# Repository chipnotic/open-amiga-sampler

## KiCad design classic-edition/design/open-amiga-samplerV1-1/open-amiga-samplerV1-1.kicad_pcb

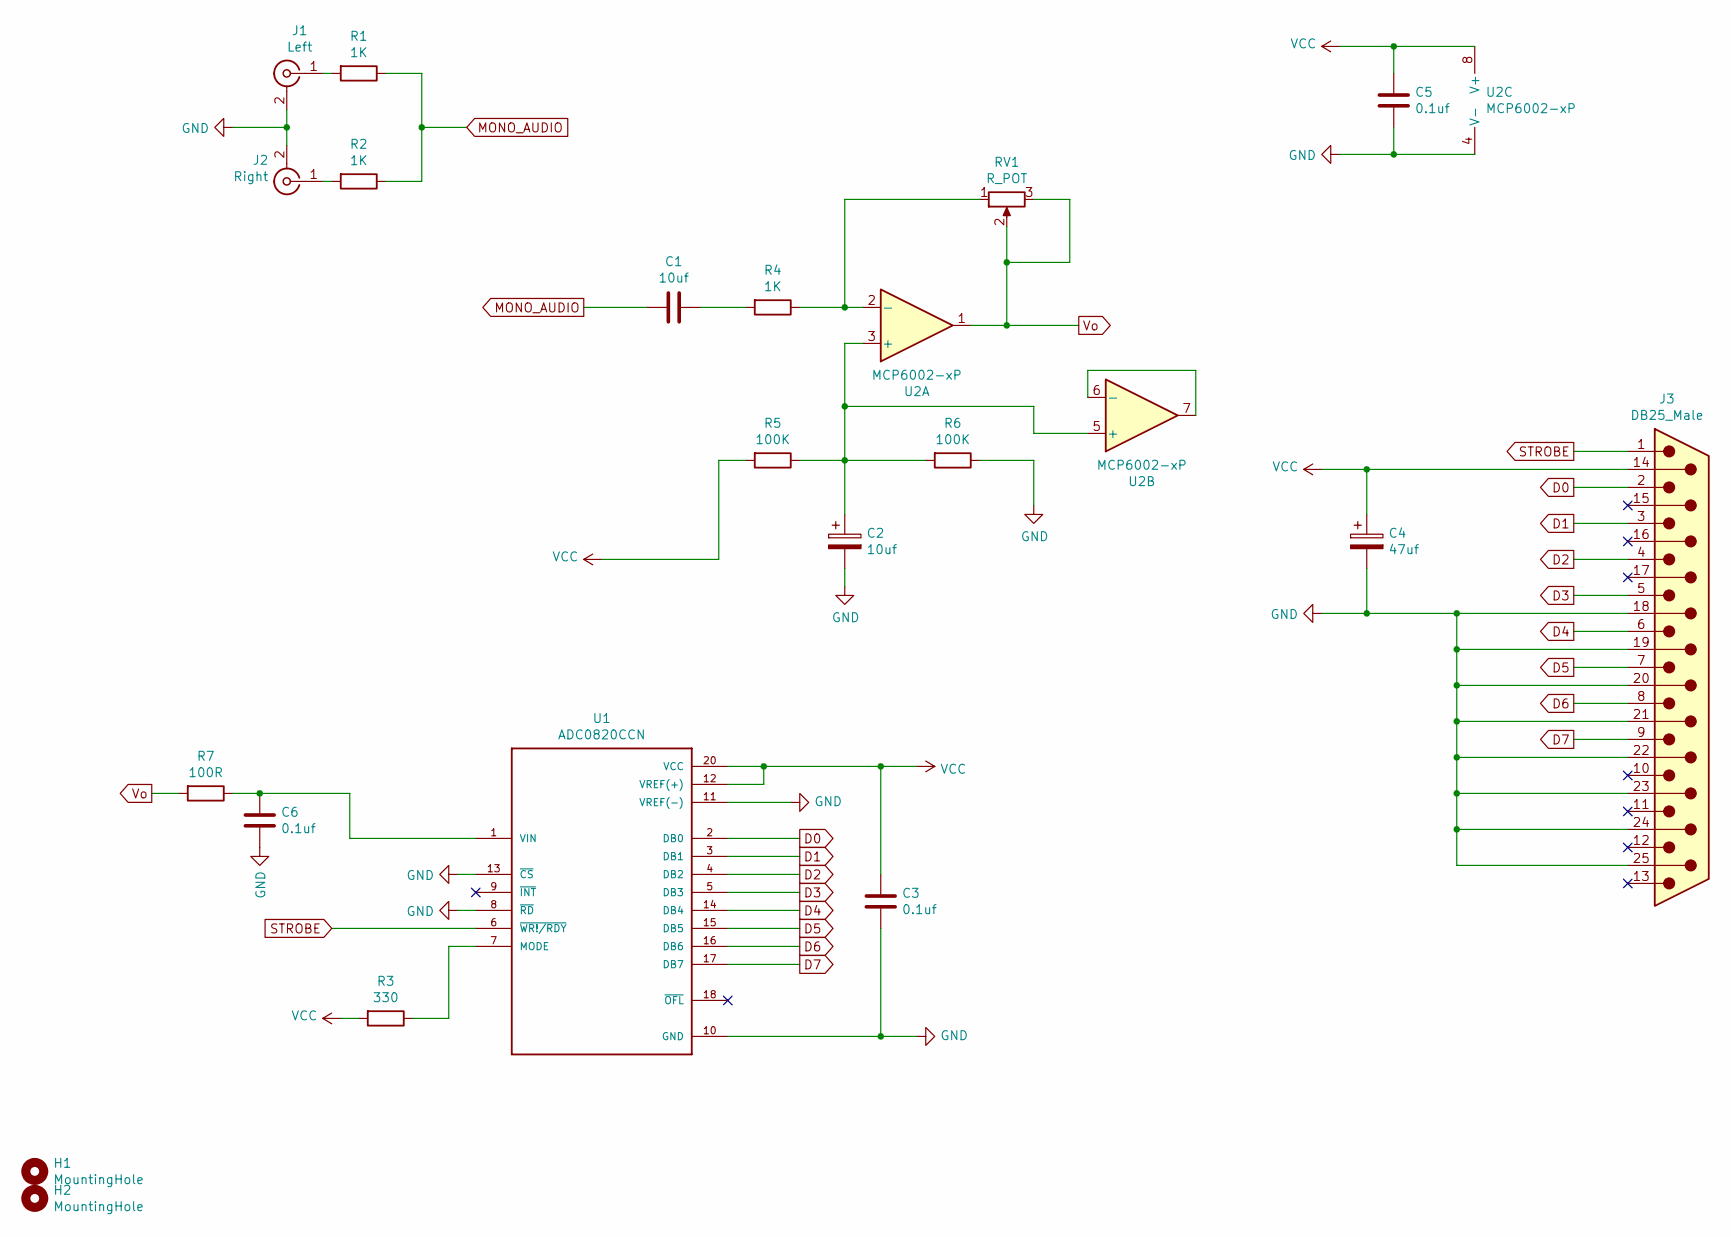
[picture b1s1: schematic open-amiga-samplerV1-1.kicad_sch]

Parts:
C1: 10uf; CP_Radial_Tantal_D5.5mm_P2.50mm; Mouser 581-TAP106K010DTW
C2: 10uf; CP_Radial_D4.0mm_P1.50mm; Mouser 647-UMP1A100MDD1TP
C3, C5, C6: 0.1uf; C_Disc_D3.4mm_W2.1mm_P2.50mm
C4: 47uf; CP_Radial_D5.0mm_P2.00mm; Mouser 647-URS1A470MDD1TA
H1, H2: MountingHole; MountingHole_2.2mm_M2
J1: Left; Audio pads; Mouser 490-RCJ-032
J2: Right; Audio pads; Mouser 490-RCJ-031
J3: DB25_Male; DSUB-25_Male_EdgeMount_P2.77mm; Mouser 601-40-9725M
R1, R2, R4: 1K; R_Axial_DIN0207_L6.3mm_D2.5mm_P10.16mm_Horizontal
R3: 330; R_Axial_DIN0207_L6.3mm_D2.5mm_P10.16mm_Horizontal
R5, R6: 100K; R_Axial_DIN0207_L6.3mm_D2.5mm_P10.16mm_Horizontal
R7: 100R; R_Axial_DIN0207_L6.3mm_D2.5mm_P10.16mm_Horizontal
RV1: R_POT; Pot pads; Mouser 858-P160KN-0QC20A10K
U1: ADC0820CCN; DIP-20_W7.62mm_Socket; Mouser 700-ADC0820CCN
U2: MCP6002-xP; DIP-8_W7.62mm_Socket; Mouser 579-MCP6002-I/P

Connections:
D0: J3.2, U1.2 (DB0)
D1: J3.3, U1.3 (DB1)
D2: J3.4, U1.4 (DB2)
D3: J3.5, U1.5 (DB3)
D4: J3.6, U1.14 (DB4)
D5: J3.7, U1.15 (DB5)
D6: J3.8, U1.16 (DB6)
D7: J3.9, U1.17 (DB7)
GND: C2.2, C3.2, C4.2, C5.2, C6.2, J1.2 (Ext), J2.2 (Ext), J3.18, J3.19, J3.20, J3.21, J3.22, J3.23, J3.24, J3.25, R6.1, U1.8 (~RD), U1.10 (GND), U1.11 (VREF(-)), U1.13 (~CS), U2.4 (V-)
MONO_AUDIO: C1.1, R1.1, R2.1
unnamed: C1.2, R4.2
unnamed: J1.1 (In), R1.2
unnamed: J2.1 (In), R2.2
unnamed: R3.1, U1.7 (MODE)
unnamed: R4.1, RV1.1, U2.2 (-)
unnamed: C6.1, R7.1, U1.1 (VIN)
unnamed: C2.1, R5.1, R6.2, U2.3 (+), U2.5 (+)
unnamed: U2.6 (-), U2.7
STROBE: J3.1, U1.6 (~WR!/RDY)
VCC: C3.1, C4.1, C5.1, J3.14, R3.2, R5.2, U1.12 (VREF(+)), U1.20 (VCC), U2.8 (V+)
Vo: R7.2, RV1.2, RV1.3, U2.1

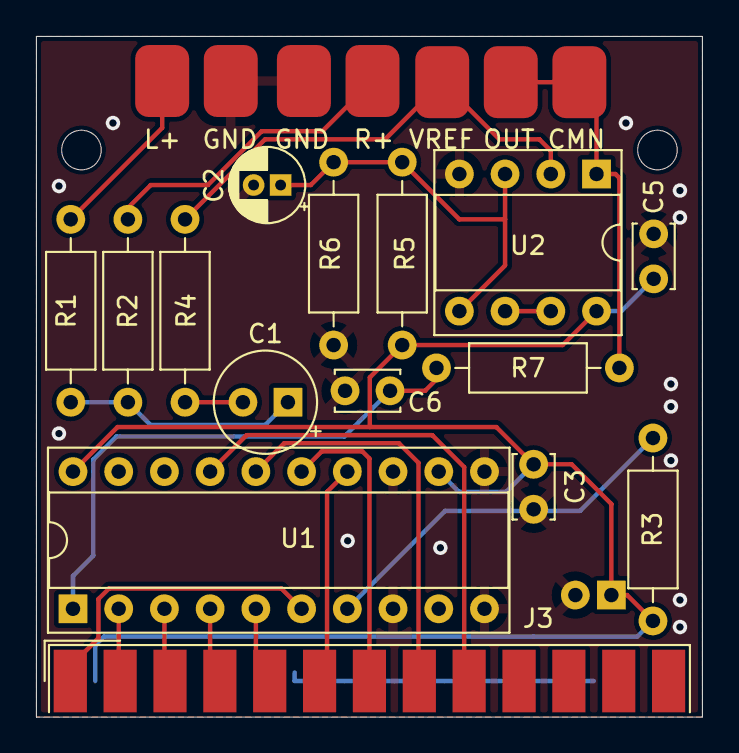
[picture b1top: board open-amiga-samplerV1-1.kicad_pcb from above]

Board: 2 copper layers, 37.0 x 37.8 mm, 21 parts (1 on the bottom side), 21 nets.

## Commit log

2022-03-19 Changes for V1.1
    Added changes to sampler as per gwEm303's V1.1 suggestions:
    DC Offset Fix - R5/R6 changed to 100k.
    C1 changed to tantalum.
    Connected unused op-amp.
    Added R7/C6 as "simple anti-aliasing filter (1st order)".
    PCB enlarged slightly to accommodate the new components, mounting holes not changed PCB just extended behind making the board slightly longer.
2022-03-19 File cleanup
